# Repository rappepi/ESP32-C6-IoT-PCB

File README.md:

# ESP32-C6-IoT-PCB

This project is licensed under the [Creative Commons Attribution-NonCommercial 4.0 International (CC BY-NC 4.0)](https://creativecommons.org/licenses/by-nc/4.0/).  
You are free to use, modify, and share the project as long as it is **not for commercial use** and **you give appropriate credit** to the original author.

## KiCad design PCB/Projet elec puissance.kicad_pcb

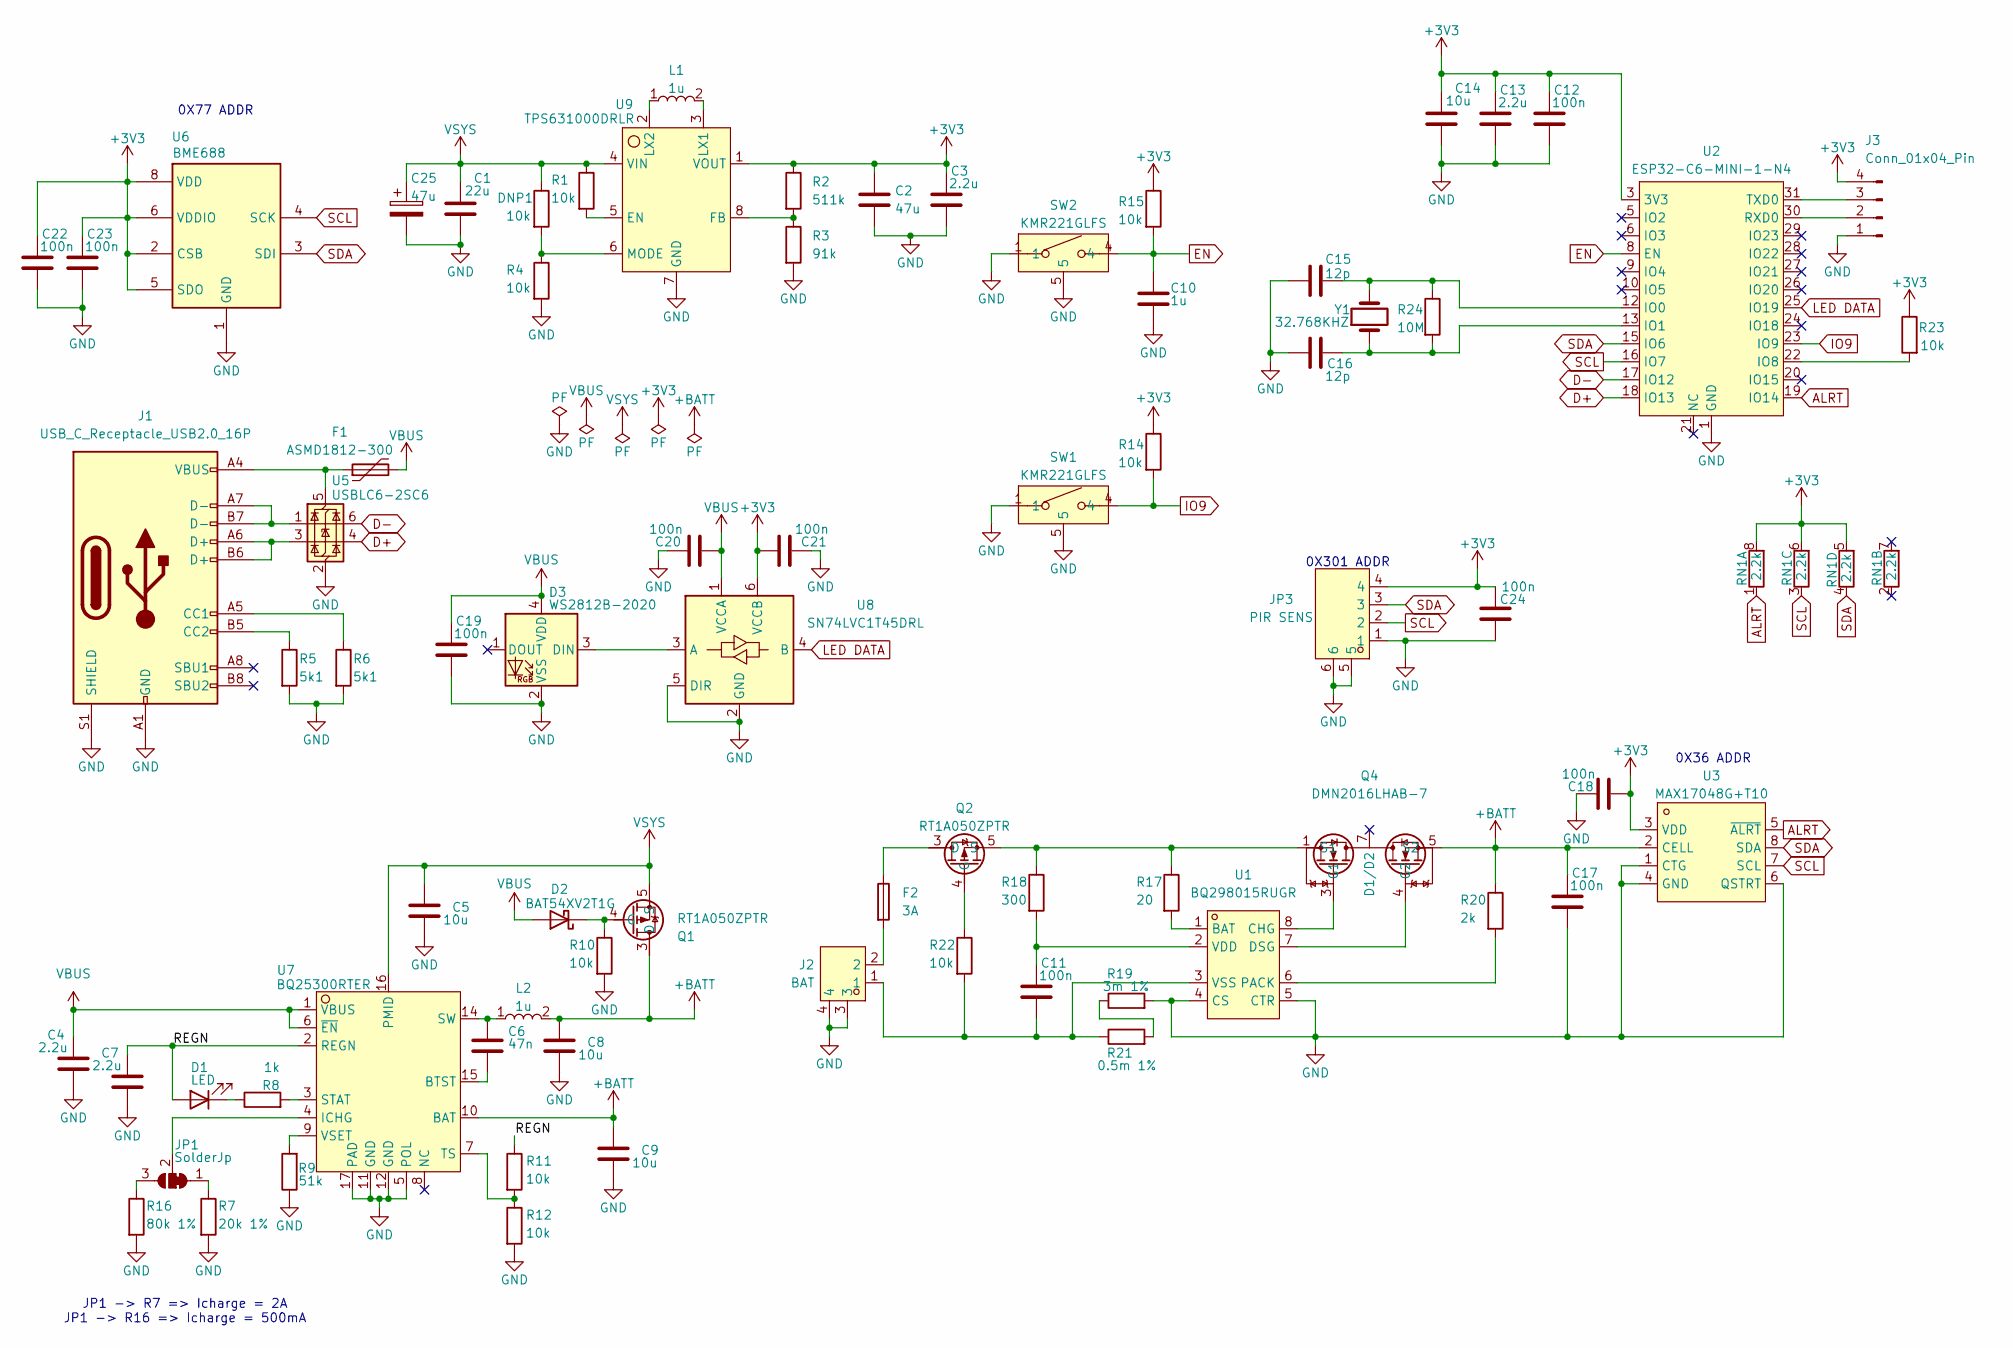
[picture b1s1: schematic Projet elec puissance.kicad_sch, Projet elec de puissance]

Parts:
C1: 22u; C_0603_1608Metric_Pad1.08x0.95mm_HandSolder; LCSC Part C361061
C2: 47u; C_0805_2012Metric_Pad1.18x1.45mm_HandSolder; LCSC Part C471380
C3, C4, C7, C13: 2.2u; C_0402_1005Metric_Pad0.74x0.62mm_HandSolder; LCSC Part C170151
C5, C8, C9, C14: 10u; C_0603_1608Metric_Pad1.08x0.95mm_HandSolder; LCSC Part C96446
C6: 47n; C_0402_1005Metric_Pad0.74x0.62mm_HandSolder; LCSC Part C307339
C10: 1u; C_0402_1005Metric_Pad0.74x0.62mm_HandSolder; LCSC Part C14445
C11, C12, C17, C18, C19, C20, C21, C22, C23, C24: 100n; C_0402_1005Metric_Pad0.74x0.62mm_HandSolder; LCSC Part C155422
C15, C16: 12p; C_0402_1005Metric_Pad0.74x0.62mm_HandSolder; LCSC Part C26406
C25: 47u; CP_EIA-6032-28_Kemet-C; LCSC Part C7219
D1: LED; LED_0402_1005Metric_Pad0.77x0.64mm_HandSolder; LCSC Part C130719
D2: BAT54XV2T1G; D_SOD-523; LCSC Part C81572
D3: WS2812B-2020; LED_WS2812B-2020_PLCC4_2.0x2.0mm; LCSC Part C965555
DNP1: 10k; R_0402_1005Metric_Pad0.72x0.64mm_HandSolder; LCSC Part C71617
F1: ASMD1812-300; R_1812_4532Metric_Pad1.30x3.40mm_HandSolder; LCSC Part C2982284
F2: 3A; Fuse_1206_3216Metric_Pad1.42x1.75mm_HandSolder; LCSC Part C14165
J1: USB_C_Receptacle_USB2.0_16P; USB_C_Receptacle_G-Switch_GT-USB-7010ASV; LCSC Part C963413
J2: BAT; CONN-SMD_SM02B-PASS-TLFSN; LCSC Part C495198
J3: Conn_01x04_Pin; PinHeader_1x04_P1.00mm_Vertical
JP1: SolderJp; SolderJumper-3_P1.3mm_Bridged12_RoundedPad1.0x1.5mm_NumberL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
JP3: PIR SENS; CONN-SMD_4P-P1.00_SM04B-SRSS-TB-LF-SN; LCSC Part C160404
L1, L2: 1u; L1008; LCSC Part C882955
Q1, Q2: RT1A050ZPTR; TSST8-8_L3.0-W1.6-P0.65-LS2.0-BL; LCSC Part C308756
Q4: DMN2016LHAB-7; U-DFN2030-6_L2.0-W3.0-P0.65-BL-EP; LCSC Part C264091
R1, R4, R10, R11, R12, R14, R15, R22, R23: 10k; R_0402_1005Metric_Pad0.72x0.64mm_HandSolder; LCSC Part C71617
R2: 511k; R_0402_1005Metric_Pad0.72x0.64mm_HandSolder; LCSC Part C64042
R3: 91k; R_0402_1005Metric_Pad0.72x0.64mm_HandSolder; LCSC Part C4147
R5, R6: 5k1; R_0402_1005Metric_Pad0.72x0.64mm_HandSolder; LCSC Part C25905
R7: 20k 1%; R_0402_1005Metric_Pad0.72x0.64mm_HandSolder; LCSC Part C25765
R8: 1k; R_0402_1005Metric_Pad0.72x0.64mm_HandSolder; LCSC Part C11702
R9: 51k; R_0402_1005Metric_Pad0.72x0.64mm_HandSolder; LCSC Part C25794
R16: 80k 1%; R_0402_1005Metric_Pad0.72x0.64mm_HandSolder; LCSC Part C25921
R17: 20; R_0402_1005Metric_Pad0.72x0.64mm_HandSolder; LCSC Part C138031
R18: 300; R_0402_1005Metric_Pad0.72x0.64mm_HandSolder; LCSC Part C25102
R19: 3m 1%; R_1206_3216Metric_Pad1.30x1.75mm_HandSolder; LCSC Part C601095
R20: 2k; R_0402_1005Metric_Pad0.72x0.64mm_HandSolder; LCSC Part C60488
R21: 0.5m 1%; R_1206_3216Metric_Pad1.30x1.75mm_HandSolder; LCSC Part C521527
R24: 10M; R_0402_1005Metric_Pad0.72x0.64mm_HandSolder; LCSC Part C26082
RN1: 2.2k; R_Array_Concave_4x0402; LCSC Part C148505
SW1, SW2: KMR221GLFS; KEY-SMD_KMR2XXGXXX; LCSC Part C72443
U1: BQ298015RUGR; X2QFN-8_L1.5-W1.5-P0.50-TL; LCSC Part C3681805
U2: ESP32-C6-MINI-1-N4; WIFIM-SMD_61P-L16.6-W13.2-P0.80-ESP32-C6-MINI-1-N4; LCSC Part C5736265
U3: MAX17048G+T10; DFN-8_L2.0-W2.0-P0.50-BL-EP; LCSC Part C2682616
U5: USBLC6-2SC6; SOT-23-6; LCSC Part C7519
U6: BME688; Bosch_LGA-8_3x3mm_P0.8mm_ClockwisePinNumbering; LCSC Part C3664478
U7: BQ25300RTER; QFN-16_L3.0-W3.0-P0.50-BL-EP1.7; LCSC Part C2763848
U8: SN74LVC1T45DRL; SOT-563; LCSC Part C352970
U9: TPS631000DRLR; SOT-583-8_L2.1-W1.2-P0.50-LS1.6-BL; LCSC Part C5219190
Y1: 32.768KHZ; Crystal_SMD_2012-2Pin_2.0x1.2mm; LCSC Part C5341285

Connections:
+3V3: C2.1, C3.1, C12.1, C13.1, C14.1, C18.2, C21.1, C22.1, C23.1, C24.1, J3.4, JP3.4, R2.1, R14.1, R15.1, R23.1, RN1.5 (R4.2), RN1.6 (R3.2), RN1.8 (R1.2), U2.3 (3V3), U3.3 (VDD), U6.2 (CSB), U6.5 (SDO), U6.6 (VDDIO), U6.8 (VDD), U8.6 (VCCB), U9.1 (VOUT)
+BATT: C8.1, C9.1, C17.1, L2.2, Q1.1 (D), Q1.2 (D), Q1.3 (D), Q1.6 (D), Q1.7 (D), Q1.8 (D), Q4.5 (S2), Q4.6 (S2), R20.1, U3.2 (CELL), U7.10 (BAT)
/REGN: C7.1, D1.2 (A), R11.1, U7.2 (REGN)
ALRT: RN1.1 (R1.1), U2.19 (IO14), U3.5 (~ALRT)
D+: U2.18 (IO13), U5.4 (I/O2)
D-: U2.17 (IO12), U5.6 (I/O1)
EN: C10.1, R15.2, SW2.3, SW2.4, U2.8 (EN)
GND: C1.2, C2.2, C3.2, C4.2, C5.2, C7.2, C8.2, C9.2, C10.2, C12.2, C13.2, C14.2, C15.2, C16.2, C17.2, C18.1, C19.2, C20.1, C21.2, C22.2, C23.2, C24.2, C25.2, D3.2 (VSS), J1.A1 (GND), J1.A12 (GND), J1.B1 (GND), J1.B12 (GND), J1.S1 (SHIELD), J2.3, J2.4, J3.1, JP3.1, JP3.5, JP3.6, R3.2, R4.2, R5.2, R6.2, R7.2, R9.1, R10.2, R12.2, R16.2, R19.2, SW1.1, SW1.2, SW1.5, SW2.1, SW2.2, SW2.5, U1.4 (CS), U1.5 (CTR), U2.1 (GND), U2.2 (GND), U2.11 (GND), U2.14 (GND), U2.36 (GND), U2.37 (GND), U2.38 (GND), U2.39 (GND), U2.40 (GND), U2.41 (GND), U2.42 (GND), U2.43 (GND), U2.44 (GND), U2.45 (GND), U2.46 (GND), U2.47 (GND), U2.48 (GND), U2.49 (GND), U2.50 (GND), U2.51 (GND), U2.52 (GND), U2.53 (GND), U3.1 (CTG), U3.4 (GND), U3.6 (QSTRT), U3.9 (EP), U5.2 (GND), U6.1 (GND), U6.7 (GND), U7.5 (POL), U7.11 (GND), U7.12 (GND), U7.17 (PAD), U8.2 (GND), U8.5 (DIR), U9.7 (GND)
IO9: R14.2, SW1.3, SW1.4, U2.23 (IO9)
LED DATA: U2.25 (IO19), U8.4 (B)
unnamed: C6.1, L2.1, U7.13 (SW), U7.14 (SW)
unnamed: D1.1 (K), R8.1
unnamed: D2.1 (K), Q1.4 (G), R10.1
unnamed: D3.3 (DIN), U8.3 (A)
unnamed: F2.1, Q2.1 (D), Q2.2 (D), Q2.3 (D), Q2.6 (D), Q2.7 (D), Q2.8 (D)
unnamed: F2.2, J2.2
unnamed: J1.A5 (CC1), R6.1
unnamed: J1.B5 (CC2), R5.1
unnamed: J1.A6 (D+), J1.B6 (D+), U5.3 (I/O2)
unnamed: J1.A7 (D-), J1.B7 (D-), U5.1 (I/O1)
unnamed: J3.2, U2.30 (RXD0)
unnamed: J3.3, U2.31 (TXD0)
unnamed: JP1.1 (A), R7.1
unnamed: JP1.3 (B), R16.1
unnamed: JP1.2 (C), U7.4 (ICHG)
unnamed: Q2.4 (G), R22.1
unnamed: Q2.5 (S), Q4.1 (S1), Q4.2 (S1), R17.1, R18.1
unnamed: Q4.3 (G1), U1.8 (CHG)
unnamed: Q4.4 (G2), U1.7 (DSG)
unnamed: R19.1, R21.2
unnamed: R17.2, U1.1 (BAT)
unnamed: R20.2, U1.6 (PACK)
unnamed: C11.1, R18.2, U1.2 (VDD)
unnamed: C11.2, J2.1, R21.1, R22.2, U1.3 (VSS)
unnamed: C15.1, R24.1, U2.12 (IO0), Y1.2
unnamed: C16.1, R24.2, U2.13 (IO1), Y1.1
unnamed: R23.2, U2.22 (IO8)
unnamed: F1.1, J1.A4 (VBUS), J1.A9 (VBUS), J1.B4 (VBUS), J1.B9 (VBUS), U5.5 (VBUS)
unnamed: C6.2, U7.15 (BTST)
unnamed: R8.2, U7.3 (STAT)
unnamed: R11.2, R12.1, U7.7 (TS)
unnamed: R9.2, U7.9 (VSET)
unnamed: R1.2, U9.5 (EN)
unnamed: R2.2, R3.1, U9.8 (FB)
unnamed: L1.2, U9.3 (LX1)
unnamed: L1.1, U9.2 (LX2)
unnamed: DNP1.2, R4.1, U9.6 (MODE)
SCL: JP3.2, RN1.3 (R3.1), U2.16 (IO7), U3.7 (SCL), U6.4 (SCK)
SDA: JP3.3, RN1.4 (R4.1), U2.15 (IO6), U3.8 (SDA), U6.3 (SDI)
VBUS: C4.1, C19.1, C20.2, D2.2 (A), D3.4 (VDD), F1.2, U7.1 (VBUS), U7.6 (~EN), U8.1 (VCCA)
VSYS: C1.1, C5.1, C25.1, DNP1.1, Q1.5 (S), R1.1, U7.16 (PMID), U9.4 (VIN)

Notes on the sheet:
0X36 ADDR
JP1 -> R7 => Icharge = 2A JP1 -> R16 => Icharge = 500mA
0X301 ADDR
0X77 ADDR

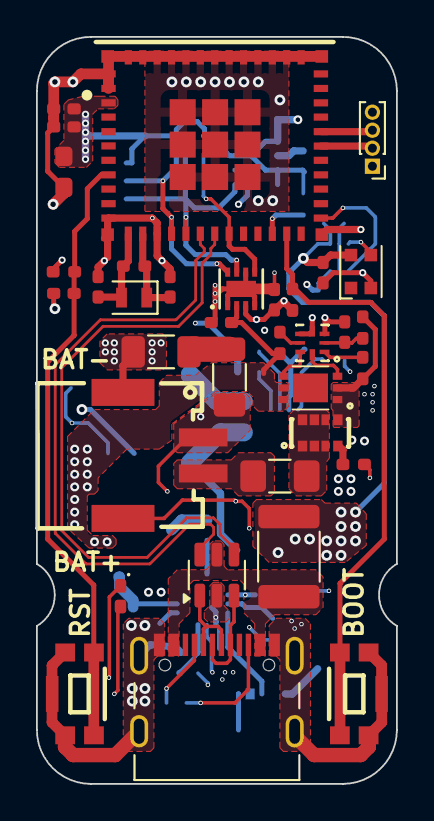
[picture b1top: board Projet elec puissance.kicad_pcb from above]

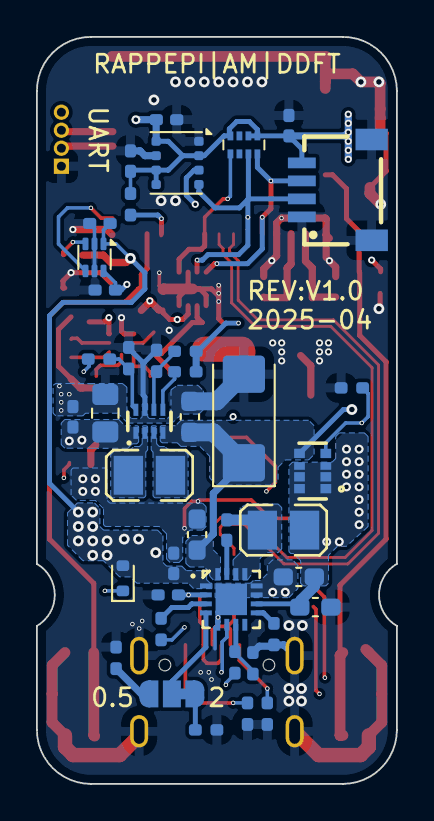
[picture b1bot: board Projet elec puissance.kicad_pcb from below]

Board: 4 copper layers, 20.0 x 41.5 mm, 76 parts (41 on the bottom side), 51 nets.

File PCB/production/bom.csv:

Designator,Footprint,Quantity,Value,LCSC Part #
C1,0603,1,22u,C361061
C10,0402,1,1u,C14445
"C11, C12, C17, C18, C19, C20, C21, C22, C23, C24",0402,10,100n,C155422
"C13, C3, C4, C7",0402,4,2.2u,C170151
"C14, C5, C8, C9",0603,4,10u,C96446
"C15, C16",0402,2,12p,C26406
C2,0805,1,47u,C471380
C25,CP_EIA-6032-28_Kemet-C,1,47u,C7219
C6,0402,1,47n,C307339
D1,0402,1,LED,C130719
D2,D_SOD-523,1,BAT54XV2T1G,C81572
D3,LED_WS2812B-2020_PLCC4_2.0x2.0mm,1,WS2812B-2020,C965555
F1,1812,1,ASMD1812-300,C2982284
F2,1206,1,3A,C14165
J1,USB_C_Receptacle_G-Switch_GT-USB-7010ASV,1,USB_C_Receptacle_USB2.0_16P,C963413
J2,CONN-SMD_SM02B-PASS-TLFSN,1,BAT,C495198
JP3,CONN-SMD_4P-P1.00_SM04B-SRSS-TB-LF-SN,1,PIR SENS,C160404
"L1, L2",L1008,2,1u,C882955
"Q1, Q2",TSST8-8_L3.0-W1.6-P0.65-LS2.0-BL,2,RT1A050ZPTR,C308756
Q4,U-DFN2030-6_L2.0-W3.0-P0.65-BL-EP,1,DMN2016LHAB-7,C264091
"R1, R10, R11, R12, R14, R15, R22, R23, R4",0402,9,10k,C71617
R16,0402,1,80k 1%,C25921
R17,0402,1,20,C138031
R18,0402,1,300,C25102
R19,1206,1,3m 1%,C601095
R2,0402,1,511k,C64042
R20,0402,1,2k,C60488
R21,1206,1,0.5m 1%,C521527
R24,0402,1,10M,C26082
R3,0402,1,91k,C4147
"R5, R6",0402,2,5k1,C25905
R7,0402,1,20k 1%,C25765
R8,0402,1,1k,C11702
R9,0402,1,51k,C25794
RN1,R_Array_Concave_4x0402,1,2.2k,C148505
"SW1, SW2",KEY-SMD_KMR2XXGXXX,2,KMR221GLFS,C72443
U1,X2QFN-8_L1.5-W1.5-P0.50-TL,1,BQ298015RUGR,C3681805
U2,WIFIM-SMD_61P-L16.6-W13.2-P0.80-ESP32-C6-MINI-1-N4,1,ESP32-C6-MINI-1-N4,C5736265
U3,DFN-8_L2.0-W2.0-P0.50-BL-EP,1,MAX17048G+T10,C2682616
U5,SOT-23-6,1,USBLC6-2SC6,C7519
U6,Bosch_LGA-8_3x3mm_P0.8mm_ClockwisePinNumbering,1,BME688,C3664478
U7,QFN-16_L3.0-W3.0-P0.50-BL-EP1.7,1,BQ25300RTER,C2763848
U8,SOT-563,1,SN74LVC1T45DRL,C352970
U9,SOT-583-8_L2.1-W1.2-P0.50-LS1.6-BL,1,TPS631000DRLR,C5219190
Y1,Crystal_SMD_2012-2Pin_2.0x1.2mm,1,32.768KHZ,C5341285

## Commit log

2025-05-14 Update README.md
    Added CC BY-NC 4.0 license
2025-05-14 Create LICENSE
    Added LICENSE
2025-09-24 PCB files added
2025-09-24 added images
2025-09-24 Fix bad image links

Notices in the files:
README.md:
License: CC BY-NC 4.0
